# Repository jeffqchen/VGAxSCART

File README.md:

# VGAxSCART

A VGAxSCART Adapter for RGBS. This is one of the different links in my [RGBS dongle series](https://github.com/jeffqchen/Console-VGA-Dongle-Series).

This dongle passes RGB and Sync video signals, as well as stereo audio between SCART and VGA. Note it does not convert H+V Sync from/into CSync.

The SCART fast switching/blanking voltage is preserved for compatibility, while the function switching/aspect ratio voltage is discarded for better safety.

This design is bi-directional. You can choose the direction during assembly by closing the corresponding jumper pads on the PCB.

3D printed shells for each direction are also provided.

--------
## Parts

- [PCB](https://oshpark.com/projects/7dVfe56C)

- VGA Port Slim, Female - [Link](https://github.com/jeffqchen/JeffParts/blob/main/Connectors/HD15/Slim/Female%20PCB/info.md)

- SCART Male Plug, Cable Type - [Link](https://github.com/jeffqchen/JeffParts/blob/main/Connectors/SCART/Male%20Cable/info.md)

- [2x] M2x20mm Screws and Nuts - [Link](https://github.com/jeffqchen/JeffParts/blob/main/Parts/M2%20M3%20Hex%20Screw%20%26%20Nut/info.md)

SMD Resistor, 0603 size
- [1x] 180 Ohm
- [1x] 470 Ohm

- 3D Printed Shell

--------
## Configuration
### Choose Bwteen In Or Out
Close the directional jumper with solder:
- Triangle: VGA to SCART
- No triangle: SCART to VGA

### Close Jumper for CVBS/LUMA Sync Signal
In case you are using CVBS or Luma as sync, close jumper JP6 next to R2.

### Shielding Connection Jumpers
The two jumpers connecting GND to each of the VGA shielding pins should be left open when it's on the sink side, and closed when it's on the source side.

--------
## Assembly

Solder the SMD resistors onto the PCB.

Insert the SCART header with its shielding into the top shell. Then fit the PCB without the VGA header in between the two rows of the contacts on the SCART header.

Press the PCB inwards and downwards to hold it in place. Solder down two contacts on the SCART header to the PCB.

Take the assembly out of the shell. Inspect if the SCART plug is straight. If the plug is crooked, melt the soldered contacts and adjust the plug until it is. Otherwise it will be very hard to close up the shell.

 Go on and solder all the rest of the contacts on the SCART header onto the PCB. Make sure the PCB is perpendicular to the bottom of the SCART header Then, solder in the VGA port.

Finally, fit the assembly back into the top shell, and close the bottom shell with the top with two sets of M2x20mm screws and nuts.

Note the screws travel in a slightly diagonal direction. Pay attention to the direction when tightening the screws.

--------

Shield: [![CC BY-SA 4.0][cc-by-sa-shield]][cc-by-sa]

This work is licensed under a
[Creative Commons Attribution-ShareAlike 4.0 International License][cc-by-sa].

[![CC BY-SA 4.0][cc-by-sa-image]][cc-by-sa]

[cc-by-sa]: http://creativecommons.org/licenses/by-sa/4.0/
[cc-by-sa-image]: https://licensebuttons.net/l/by-sa/4.0/88x31.png
[cc-by-sa-shield]: https://img.shields.io/badge/License-CC%20BY--SA%204.0-lightgrey.svg

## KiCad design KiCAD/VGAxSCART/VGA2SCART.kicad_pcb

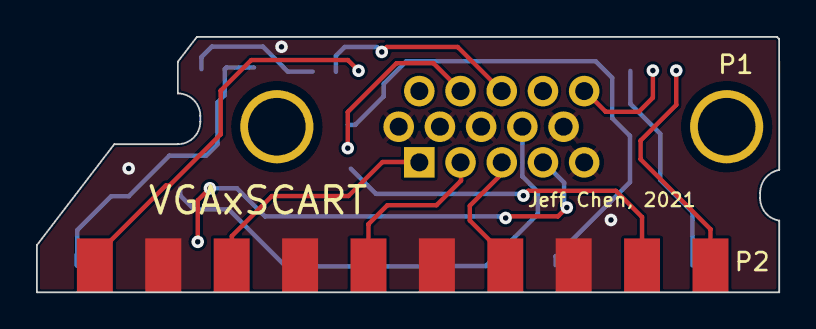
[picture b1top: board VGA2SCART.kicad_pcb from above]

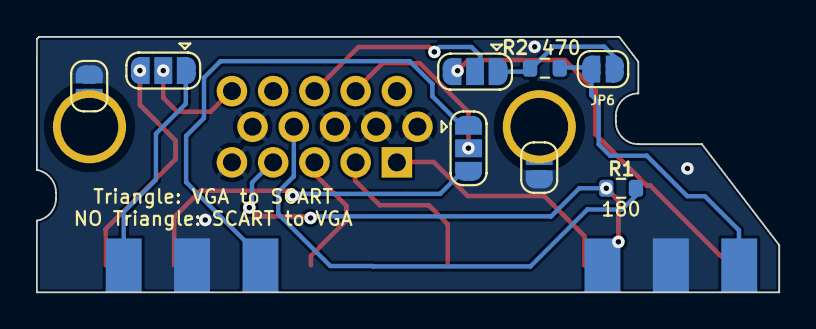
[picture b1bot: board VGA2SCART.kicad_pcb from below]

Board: 2 copper layers, 41.2 x 14.2 mm, 10 parts (8 on the bottom side), 18 nets.

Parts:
JP1, JP2, JP3: SolderJumper_3_Open; SolderJumper-3_P1.3mm_Open_RoundedPad1.0x1.5mm
JP4, JP5: SolderJumper_2_Open; SolderJumper-2_P1.3mm_Open_RoundedPad1.0x1.5mm
JP6: No Attenuation; SolderJumper-2_P1.3mm_Open_RoundedPad1.0x1.5mm
P1: VGA; VGA_female_rightangle_slim
P2: SCART_PAL; SCART_Cutdown
R1: 180 Ohm; R_0603_1608Metric
R2: 470; R_0603_1608Metric

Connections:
/Attenuated_Sync: JP1.1 (A), JP6.1 (A), R2.1
/Audio_L_In: JP2.1 (A), P2.6 (Audio_L_In)
/Audio_L_Out: JP2.3 (B), P2.3 (Audio_L_Out)
/Audio_R_In: JP3.1 (A), P2.2 (Audio_R_In)
/Audio_R_Out: JP3.3 (B), P2.1 (Audio_R_Out)
/Blanking: P1.4 (ID2/RES), P2.16 (Fast_switching), R1.2
/Blue: P1.3 (Blue), P2.7 (Blue)
/CVBS_In: JP6.2 (B), P2.20 (CVBS_In), R2.2
/CVBS_Out: JP1.3 (B), P2.19 (CVBS_Out)
/Green: P1.2 (Green), P2.11 (Green)
/Red: P1.1 (Red), P2.15 (Red)
/Sync: JP1.2 (C), P1.13 (HSYNC)
/VGA_Audio_L: JP2.2 (C), P1.12 (ID1/SDA)
/VGA_Audio_R: JP3.2 (C), P1.15 (ID3/SCL)
GND: JP4.2 (B), JP5.2 (B), P1.5 (HSYNC_GND), P1.6 (Red_GND), P1.7 (Green_GND), P1.8 (Blue_GND), P1.10 (VSYNC_GND), P2.4 (Audio_GND), P2.5 (Blue_GND), P2.9 (Green_GND), P2.13 (Red_GND), P2.17 (CVBS_Out_GND), P2.18 (CVBS_In_GND)
unnamed: JP4.1 (A), P1.S1 (SHIELD)
unnamed: JP5.1 (A), P1.S2 (SHIELD)
unnamed: P1.9 (+5V), R1.1

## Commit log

2021-11-15 Initial Upload
2021-11-29 Update photos
2022-08-09 Change license type
2023-02-17 Add Jumper for Non-CSync
